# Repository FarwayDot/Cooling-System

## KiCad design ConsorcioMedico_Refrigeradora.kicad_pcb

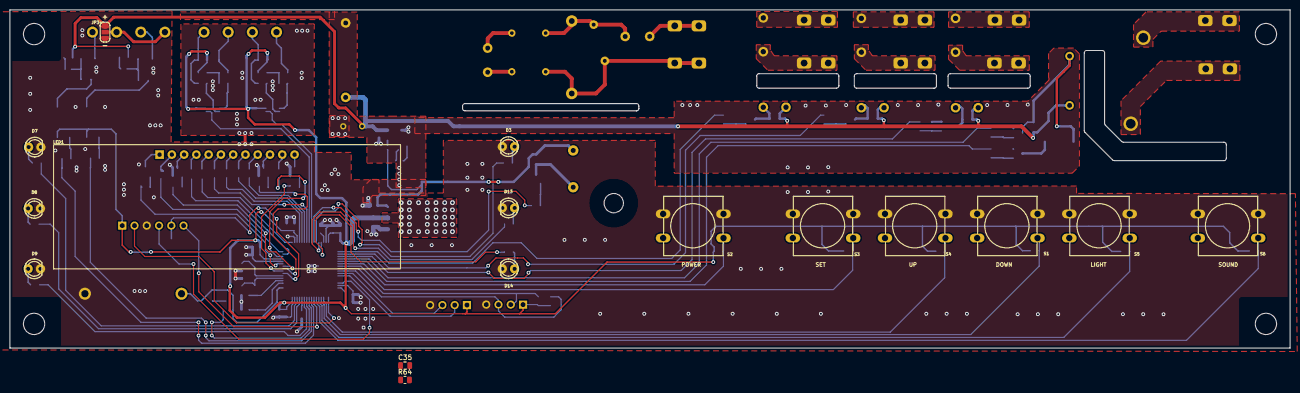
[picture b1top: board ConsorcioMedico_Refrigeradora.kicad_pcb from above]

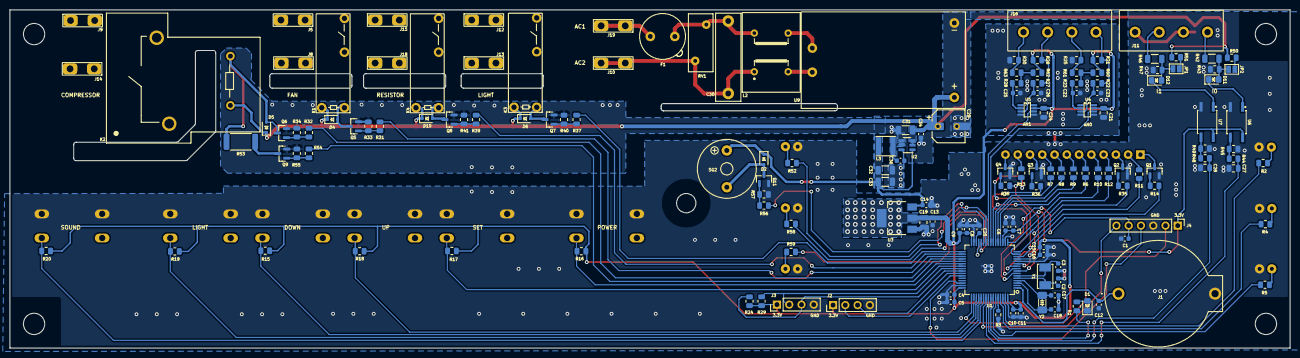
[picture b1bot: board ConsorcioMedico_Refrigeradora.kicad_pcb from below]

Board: 2 copper layers, 265.0 x 70.0 mm, 171 parts (153 on the bottom side), 126 nets.

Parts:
C1, C4, C6, C8, C10, C12, C13, C14, C15, C34: 100nF 50V; C_0603_1608Metric
C2, C3: 30pF 50V; C_0603_1608Metric
C5, C7, C9, C11: 10nF 50V; C_0603_1608Metric
C16, C22, C23, C25, C26: 1uF 50V; C_0603_1608Metric
C17, C18: 15pF 10V; C_0603_1608Metric
C19: 4.7uF 5V; C_0805_2012Metric
C20: 2.2uF 50V; C_0603_1608Metric
C21, C24: 100nF 50V; C_0805_2012Metric
C27, C28, C35: 1uF 50V; C_0805_2012Metric
C29: 100uF 25V; CP_Elec_6.3x7.7
C30: 0.1uF 275VAC; C_Rect_L18.0mm_W5.0mm_P15.00mm_FKS3_FKP3
C31: 10uF; C_1206_3216Metric
C32, C33: 22uF; C_1206_3216Metric
C36: 100nF; C_0603_1608Metric
D1: LED_0805
D2, D4, D5, D6, D10: 1N4148WS; D_SOD-323
D3: Powe_State; LED_3mm
D7: Cooling_State; LED_3mm
D8: Defroting_State; LED_3mm
D9: Fan_State; LED_3mm
D11, D12: RED; LED_0805
D13: Button_Lock; LED_3mm
D14: Door_State; LED_3mm
F1: 250VAC 0.5AAC; Fuseholder_TR5_Littelfuse_No560_No460
J1: BatteryHolder; BatteryHolder_DS1092_04_B6P
J2: USART; PinHeader_1x04_P2.54mm_Vertical
J3: I2C; PinHeader_1x04_P2.54mm_Vertical
J4: SWD; PinHeader_1x06_P2.54mm_Vertical
J5, J8: Evap_fan; Solder-Terminal_FS1536_6.3x0.8mm_NINIGI
J6, J7: Screw_Terminal_01x01; Pad_0.7mm_1.3mm
J9, J14: Compress; Solder-Terminal_FS1536_6.3x0.8mm_NINIGI
J10, J19: AC; Solder-Terminal_FS1536_6.3x0.8mm_NINIGI
J11: Digital; Terminal-Block_XY2500V-B_4P_P5.0mm_XINYA
J12, J13: Light; Solder-Terminal_FS1536_6.3x0.8mm_NINIGI
J15, J18: Resistor; Solder-Terminal_FS1536_6.3x0.8mm_NINIGI
J16: Analog; Terminal-Block_XY2500V-B_4P_P5.0mm_XINYA
JP1, JP2: Bridge1; SolderJumper-2_P1.3mm_Open_Pad1.0x1.5mm
JP3: SolderJumper_3_Open; SolderJumper-3_P1.3mm_Open_RoundedPad1.0x1.5mm
K1, K3, K4: HF46F-G/012-HS1T; Relay_HONGFA_SPST-NO_20.5x7x15.3mm
K2: AZ2150-1A-12DEF; Relay_Zettler_SPST-NO_31.8x26.9x19.1mm
L2: UU9.8-10mH
L3: YNR4030-4R7M 4.7uF; Inductor_YNR4030_4x4x3mm_YJYCOIN
LED1: LFD080AUE-103A-0
Q1, Q2, Q3, Q4: MMBT3904; SOT-23
Q5, Q6, Q7, Q8, Q9, Q11: BSS806; SOT-23
R1, R14, R22, R23, R25, R27, R28, R30, R35, R36, R38, R44, R48, R64: 1k; R_0805_2012Metric
R2, R4, R5, R52, R58, R59: 560R; R_0805_2012Metric
R3: 10k; R_0603_1608Metric
R6, R7, R8, R9, R10, R11, R12, R13: 120R; R_0805_2012Metric
R15, R45, R49: 22k; R_0805_2012Metric
R16, R17, R18, R19, R20, R21, R26, R60, R62: 10k; R_0805_2012Metric
R24, R29: 2.2k; R_0805_2012Metric
R31, R32, R37, R39, R54, R56: 220R; R_0805_2012Metric
R33, R34, R40, R41, R55, R57: 10K; R_0805_2012Metric
R42, R46: 6.2k; R_1206_3216Metric
R43, R47: 2.4k; R_0805_2012Metric
R50, R51: 2k; R_0805_2012Metric
R53: 150R; R_2512_6332Metric
R61, R63: 910R; R_0805_2012Metric
RV1: RM10D561KD24E100; RV_Disc_D12mm_W5.1mm_P7.5mm
S1: Buzz; SW_PUSH-12mm-H
S2: Touch; SW_PUSH-12mm-H
S3: Up; SW_PUSH-12mm-H
S4: Down; SW_PUSH-12mm-H
S5: Cooling; SW_PUSH-12mm-H
S6: Light; SW_PUSH-12mm-H
SG2: F_TMB
U1: STM32F411RETx; LQFP-64_10x10mm_P0.5mm
U2: AP63205WU; TSOT-23-6
U3: LDL1117; SOT-223-3_TabPin2
U4, U5: INA350; SOT-23-8
U6, U7: LTV-357T; SO-4_4.4x3.6mm_P2.54mm
U9: HLK-PMx; HLK-PM12
Y1: 8Mhz; Crystal_SMD_5032-2Pin_5.0x3.2mm
Y2: 32.768khz/12.5pF; Crystal_SMD_3215-2P_32.768khz

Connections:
+3.3V: C4.1, C5.1, C6.1, C7.1, C8.1, C9.1, C10.1, C11.1, C13.1, C15.1, C16.1, C19.1, C21.1, C24.1, J2.1, J3.1, J4.1, R15.2, R16.2, R17.2, R18.2, R19.2, R20.2, R21.1, R24.2, R26.1, R29.2, R60.1, R62.1, U1.13 (VDDA), U1.19 (VDD), U1.32 (VDD), U1.48 (VDD), U1.64 (VDD), U3.2 (VO), U4.7 (V+), U5.7 (V+), U6.4, U7.4
+5V: C14.1, C32.1, C33.1, D2.1 (K), L3.2, SG2.+, U2.1 (FB), U3.3 (VI)
+12V: C29.1, C31.1, C34.1, D4.1 (K), D5.1 (K), D6.1 (K), D10.1 (K), J6.1, JP3.1 (A), K1.2, K2.2, K3.2, K4.2, R50.2, R51.2, U2.2 (EN), U2.3 (IN), U9.3 (+)
+BATT: C12.1, J1.1, U1.1 (VBAT)
A: R13.1, U1.14 (PA0)
B: R12.1, U1.15 (PA1)
Button_Down: C35.1, R64.1, U1.52 (PC11)
Button_Light: R19.1, S5.1, U1.53 (PC12)
Button_Power: R16.1, S2.1, U1.38 (PC7)
Button_Set: R17.1, S3.1, U1.39 (PC8)
Button_Sound: R20.1, S6.1, U1.54 (PD2)
Button_Up: R18.1, S4.1, U1.51 (PC10)
C: R11.1, U1.16 (PA2)
D: R10.1, U1.17 (PA3)
DIG1: R14.1, U1.11 (PC3)
DIG2: R35.1, U1.10 (PC2)
DIG3: R36.1, U1.9 (PC1)
DIG4: R38.1, U1.8 (PC0)
DIG_IN_0: C27.1, R44.2, U1.56 (PB4)
DIG_IN_1: C28.1, R48.2, U1.57 (PB5)
DP: R6.1, U1.23 (PA7)
E: R9.1, U1.20 (PA4)
F: R8.1, U1.21 (PA5)
G: R7.1, U1.22 (PA6)
GND: C1.2, C2.2, C3.2, C4.2, C5.2, C6.2, C7.2, C8.2, C9.2, C10.2, C11.2, C12.2, C13.2, C14.2, C15.2, C16.2, C17.2, C18.2, C19.2, C20.2, C21.2, C22.2, C23.2, C24.2, C25.2, C26.2, C27.2, C28.2, C29.2, C31.2, C32.2, C33.2, C34.2, C35.2, D1.1 (K), D3.K, D7.K, D8.K, D9.K, D13.K, D14.K, J1.2, J2.4, J3.4, J4.3, J7.1, JP3.3 (B), Q1.2 (E), Q2.2 (E), Q3.2 (E), Q4.2 (E), Q5.2 (S), Q6.2 (S), Q7.2 (S), Q8.2 (S), Q9.2 (S), Q11.2 (S), R3.2, R25.2, R30.2, R33.1, R34.1, R40.1, R41.1, R43.2, R45.2, R47.2, R49.2, R55.1, R57.1, S1.3, S1.4, S2.3, S2.4, S3.3, S3.4, S4.3, S4.4, S5.3, S5.4, S6.3, S6.4, U1.12 (VSSA), U1.18 (VSS), U1.31 (VSS), U1.47 (VSS), U1.63 (VSS), U2.4 (GND), U3.1 (ADJ), U4.4 (V-), U4.5 (REF), U5.4 (V-), U5.5 (REF), U6.2, U7.2, U9.4 (-)
I0: J11.1, R42.1
I1: J11.3, R46.1
I2C3_SCL: J3.3, R24.1, U1.41 (PA8)
I2C3_SDA: J3.2, R29.1, U1.40 (PC9)
Led_Button_Lock: R58.1, U1.28 (PB2)
Led_Cooling_State: R2.1, U1.62 (PB9)
Led_Defroting_State: R4.1, U1.61 (PB8)
Led_Door_State: R59.1, U1.29 (PB10)
Led_Fan_State: R5.1, U1.59 (PB7)
Led_Power_State: R52.1, U1.27 (PB1)
Led_Status: R1.1, U1.58 (PB6)
MCU_RX1: J2.2, U1.43 (PA10)
MCU_TX1: J2.3, U1.42 (PA9)
unnamed: C30.1, F1.2, L2.4, RV1.1
unnamed: D1.2 (A), R1.2
unnamed: D2.2 (A), Q11.3 (D), SG2.-
unnamed: D3.A, R52.2
unnamed: D4.2 (A), K1.1, Q5.3 (D)
unnamed: D5.2 (A), K2.1, Q6.3 (D), R53.1
unnamed: D6.2 (A), K3.1, Q7.3 (D)
unnamed: D7.A, R2.2
unnamed: D8.A, R4.2
unnamed: D9.A, R5.2
unnamed: D10.2 (A), K4.1, Q8.3 (D)
unnamed: D11.2 (A), JP2.2 (B), R42.2, R43.1
unnamed: D11.1 (K), U6.1
unnamed: D12.2 (A), JP1.2 (B), R46.2, R47.1
unnamed: D12.1 (K), U7.1
unnamed: D13.A, R58.2
unnamed: D14.A, R59.2
unnamed: J5.1, K1.4
unnamed: J8.1, K1.3
unnamed: J9.1, K2.4
unnamed: C30.2, J10.1, L2.1, RV1.2
unnamed: J11.2, J11.4, JP3.2 (C)
unnamed: J12.1, K3.4
unnamed: J13.1, K3.3
unnamed: J14.1, K2.3
unnamed: J15.1, K4.4
unnamed: J16.1, R21.2, R22.1
unnamed: J16.2, R25.1, R61.2
unnamed: J16.3, R26.2, R27.1
unnamed: J16.4, R30.1, R63.2
unnamed: J18.1, K4.3
unnamed: F1.1, J19.1
unnamed: JP1.1 (A), R51.1
unnamed: JP2.1 (A), R50.1
unnamed: LED1.11 (A), R13.2
unnamed: LED1.4 (B), R12.2
unnamed: LED1.2 (C), R11.2
unnamed: LED1.5 (D), R10.2
unnamed: LED1.1 (DIG1), Q1.3 (C)
unnamed: LED1.3 (DIG2), Q2.3 (C)
unnamed: LED1.10 (DIG3), Q3.3 (C)
unnamed: LED1.12 (DIG4), Q4.3 (C)
unnamed: LED1.6 (DP), R6.2
unnamed: LED1.7 (E), R9.2
unnamed: LED1.8 (F), R8.2
unnamed: LED1.9 (G), R7.2
unnamed: Q1.1 (B), R14.2
unnamed: Q2.1 (B), R35.2
unnamed: Q3.1 (B), R36.2
unnamed: Q4.1 (B), R38.2
unnamed: Q5.1 (G), R31.2, R33.2
unnamed: Q6.1 (G), R32.2, R34.2
unnamed: Q7.1 (G), R37.2, R40.2
unnamed: Q8.1 (G), R39.2, R41.2
unnamed: Q9.3 (D), R53.2
unnamed: Q9.1 (G), R54.2, R55.2
unnamed: Q11.1 (G), R56.2, R57.2
unnamed: R15.1, R64.2, S1.1
unnamed: R23.1, R60.2, R61.1
unnamed: R28.1, R62.2, R63.1
unnamed: R44.1, R45.1, U6.3
unnamed: R48.1, R49.1, U7.3
unnamed: R3.1, U1.60 (BOOT0)
unnamed: C18.1, U1.3 (PC14), Y2.2
unnamed: C17.1, U1.4 (PC15), Y2.1
unnamed: C2.1, U1.5 (PH0), Y1.1
unnamed: C3.1, U1.6 (PH1), Y1.2
unnamed: C20.1, U1.30 (VCAP1)
unnamed: C36.2, U2.6 (BST)
unnamed: C36.1, L3.1, U2.5 (SW)
unnamed: C23.1, R22.2, U4.3 (+)
unnamed: C22.1, R23.2, U4.2 (-)
unnamed: C26.1, R27.2, U5.3 (+)
unnamed: C25.1, R28.2, U5.2 (-)
unnamed: L2.3, U9.1 (AC1)
unnamed: L2.2, U9.2 (AC2)
RESET: C1.1, J4.5, U1.7 (NRST)
RTD1: U1.24 (PC4), U4.6
RTD2: U1.25 (PC5), U5.6
Relay_Calefac: R39.1, U1.34 (PB13)
Relay_Compressor: R32.1, U1.36 (PB15)
Relay_Compressor_Save: R54.1, U1.37 (PC6)
Relay_Fan: R31.1, U1.35 (PB14)
Relay_Light: R37.1, U1.33 (PB12)
Relay_On: R56.1, U1.26 (PB0)
SWCLK: J4.2, U1.49 (PA14)
SWDIO: J4.4, U1.46 (PA13)
SWO: J4.6, U1.55 (PB3)

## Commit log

2023-12-28 Primer commit con el proyecto vacío
2023-12-28 SCH: Se añadió el uC, pulsadores, display, fuente, relays (aunque falta escoger el correcto)
2023-12-29 Commit de guardado
2023-12-30 SCH: Aún queda resolver la entrada digital para el switch y la fuente de voltaje. PCB: Se están acomodando los componentes
2023-12-30 SCH: Se guarda antes de crer las hojas jerárquicas
2023-12-30 SCH: Falta definir los capacitores de entrada, colocar el footprint del diodo e inductor. PCB: Falta acomodar algunos componentes.
2024-01-02 SCH: Se cambió el IRM, se colocó filtro en la entrada AC, se modificó la fuente switching LM, se corrigieron algunos errores de diseño. PCB: Se terminó el placement de los componentes
2024-01-02 Se guarda avance
2024-01-03 SCH: Se cambian la bornera por terminales, se añade un disparo más para el compressor (falta conectarlo al uC), falta modificar, se cambia la fuente switching por otra de menos costo
2024-01-03 SCH: Se modificó la posición de algunos pines para mejorar la calidad del ruteado. PCB: Se enruta las señales, quedando la alimentación, pines de programación, relays y planos de gnd
2024-01-04 SCH: Se añadieron pads en el capacitor de la fuente principal en caso de que el de tipo SMD no dure mucho. PCB: Se enrutó, se colocaron los planos GND, se acomodó la serigrafía
2024-01-04 SCH: Se modicaron algunos valores y comentarios del sch. PCB: Posiblemente debido a jlcpcb. JLCPCB: Se asigna el código para la soldura
2024-01-05 SCH: Se arregló la posición de los pulsadores, se agrega buzzer, PCB: Se revisan los componentes y se agrega serigrafía. JLCPCB: Actualizado
2024-01-05 SCH: pin EN se corrige para activar la alimentación de 5V, se cambia el empaquetado de varias resistencias 0603 a 0805. PCB: Se alarga el plano de GND, se acomodan los componentes 0805, se completa d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
2024-01-05 PCB: Se ajusta el ancho de pista a 4mm del compressor
2024-01-19 Placa_v2: Version de la tarjeta añadiendo 3 leds al costado derecho, se necesitará mover fuente de poder y acomodar. SCH: Se ha cambiado el nombre del conector USART a I2C
2024-01-20 SCH:Se modifica los leds y nombres, en este punto, posibilemente se cambie el tamaño de la placa
2024-01-22 Luego de modificaciones de Dandy
